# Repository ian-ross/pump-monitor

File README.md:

# pump-monitor
IoT system for pump shaft monitoring

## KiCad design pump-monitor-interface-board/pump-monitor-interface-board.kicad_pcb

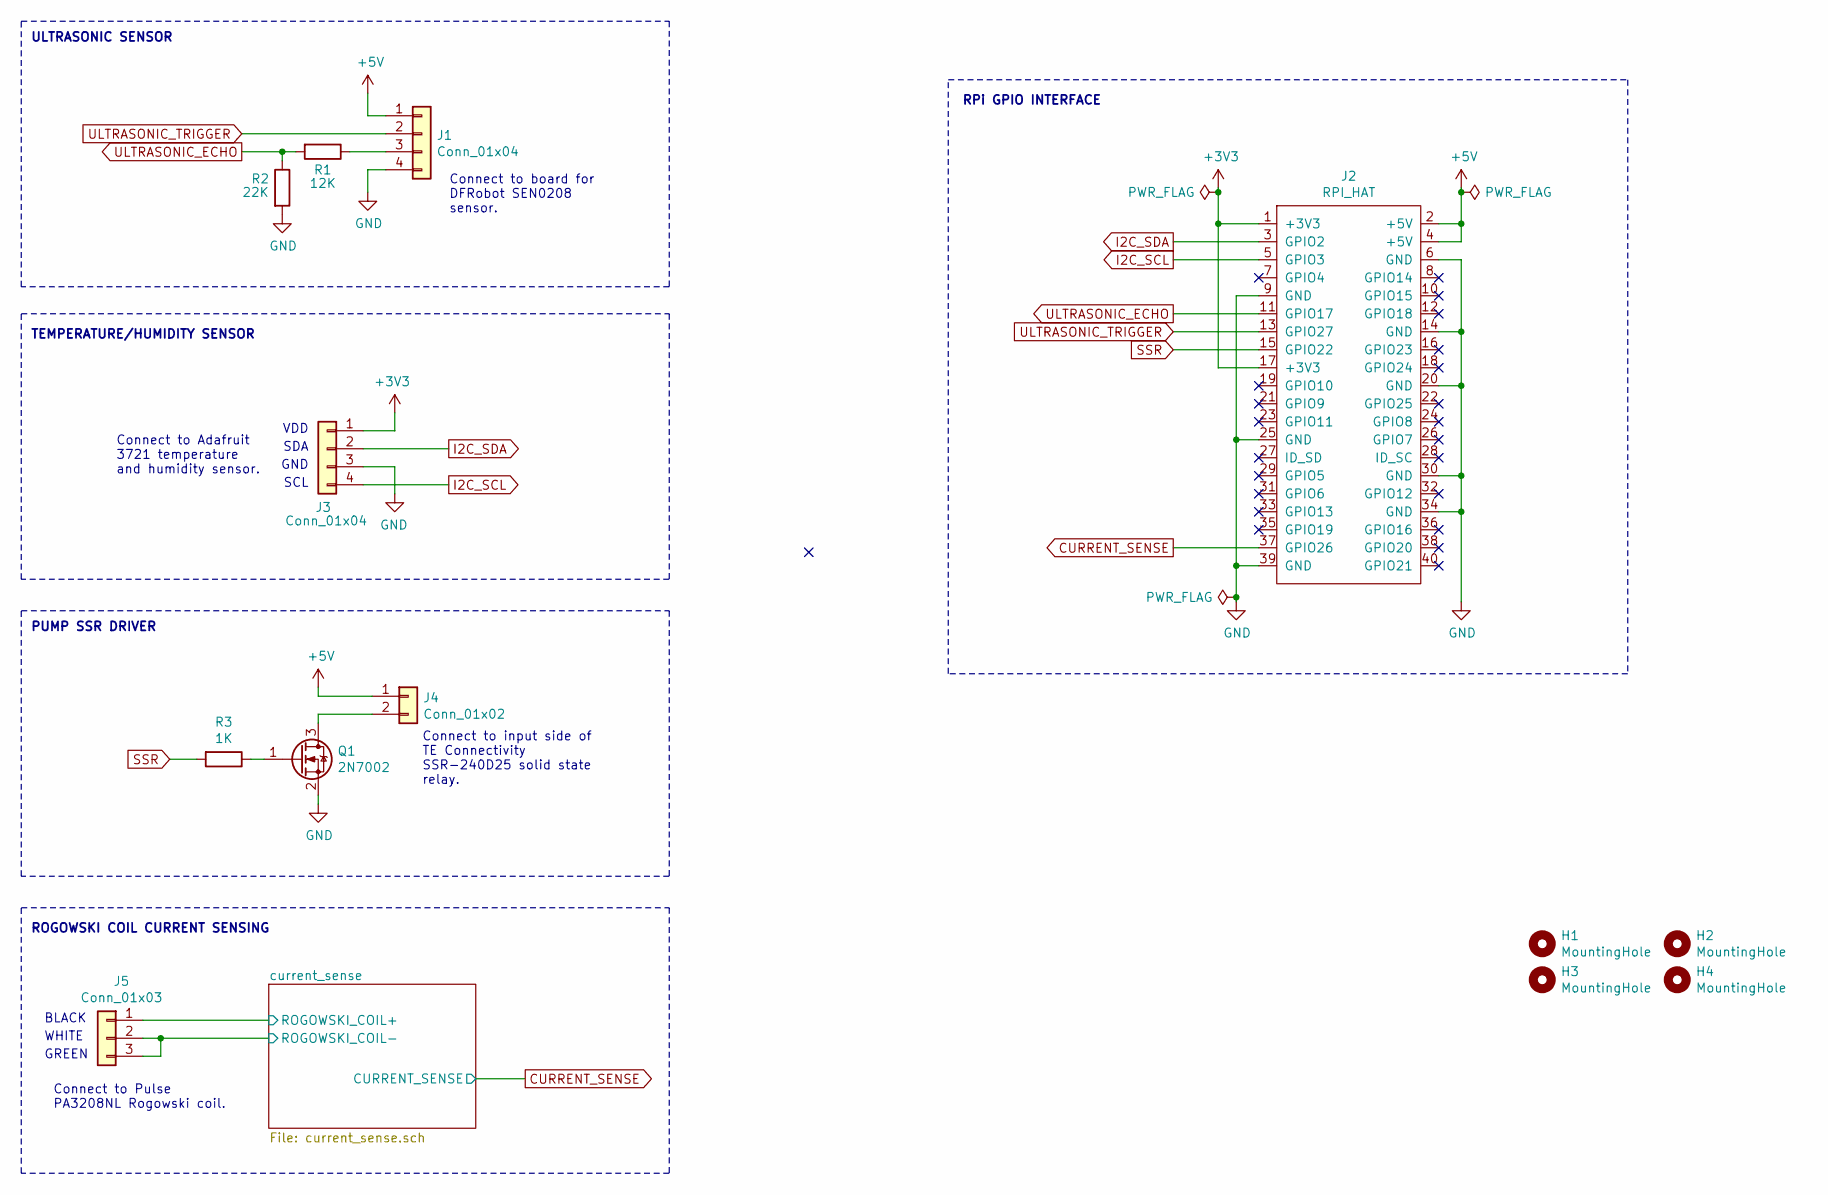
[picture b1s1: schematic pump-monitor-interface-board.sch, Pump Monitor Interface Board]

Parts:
H1, H2, H3, H4: MountingHole; MountingHole_2.7mm_M2.5; MPN n/a
J1, J3: Conn_01x04; PinHeader_1x04_P2.54mm_Horizontal; MPN TSW-104-25-T-S-RA
J2: RPI_HAT; PinSocket_2x20_P2.54mm_Vertical; MPN SSQ-120-01-L-D
J4: Conn_01x02; PinHeader_1x02_P2.54mm_Horizontal; MPN TSW-102-25-T-S-RA
J5: Conn_01x03; PinHeader_1x03_P2.54mm_Horizontal; MPN TSW-103-25-F-S-RA
Q1: 2N7002; SOT-23; MPN 2N7002ET7G
R1: 12K; R_0805_2012Metric_Pad1.20x1.40mm_HandSolder; MPN CRCW080512K0FKEA
R2: 22K; R_0805_2012Metric_Pad1.20x1.40mm_HandSolder; MPN CRCW080522K0FKEAC
R3: 1K; R_0805_2012Metric_Pad1.20x1.40mm_HandSolder; MPN CRGP0805F1K0

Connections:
+2V5: J5.2, J5.3; also elsewhere on the board
+3V3: J2.1 (+3V3), J2.17 (+3V3), J3.1
+5V: J1.1, J2.2 (+5V), J2.4 (+5V), J4.1; also elsewhere on the board
/current_sense/ROGOWSKI_COIL+: J5.1; also elsewhere on the board
CURRENT_SENSE: J2.37 (GPIO26); also elsewhere on the board
GND: J1.4, J2.6 (GND), J2.9 (GND), J2.14 (GND), J2.20 (GND), J2.25 (GND), J2.30 (GND), J2.34 (GND), J2.39 (GND), J3.3, Q1.2 (S), R2.2; also elsewhere on the board
I2C_SCL: J2.5 (GPIO3), J3.4
I2C_SDA: J2.3 (GPIO2), J3.2
unnamed: J1.3, R1.1
unnamed: J4.2, Q1.3 (D)
unnamed: Q1.1 (G), R3.1
SSR: J2.15 (GPIO22), R3.2
ULTRASONIC_ECHO: J2.11 (GPIO17), R1.2, R2.1
ULTRASONIC_TRIGGER: J1.2, J2.13 (GPIO27)

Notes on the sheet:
Connect to Pulse PA3208NL Rogowski coil.
RPi GPIO INTERFACE
BLACK
WHITE
GREEN
ROGOWSKI COIL CURRENT SENSING
PUMP SSR DRIVER
TEMPERATURE/HUMIDITY SENSOR
ULTRASONIC SENSOR
VDD
SDA
GND
SCL
Connect to Adafruit 3721 temperature and humidity sensor.
Connect to input side of TE Connectivity SSR-240D25 solid state relay.
Connect to board for DFRobot SEN0208 sensor.

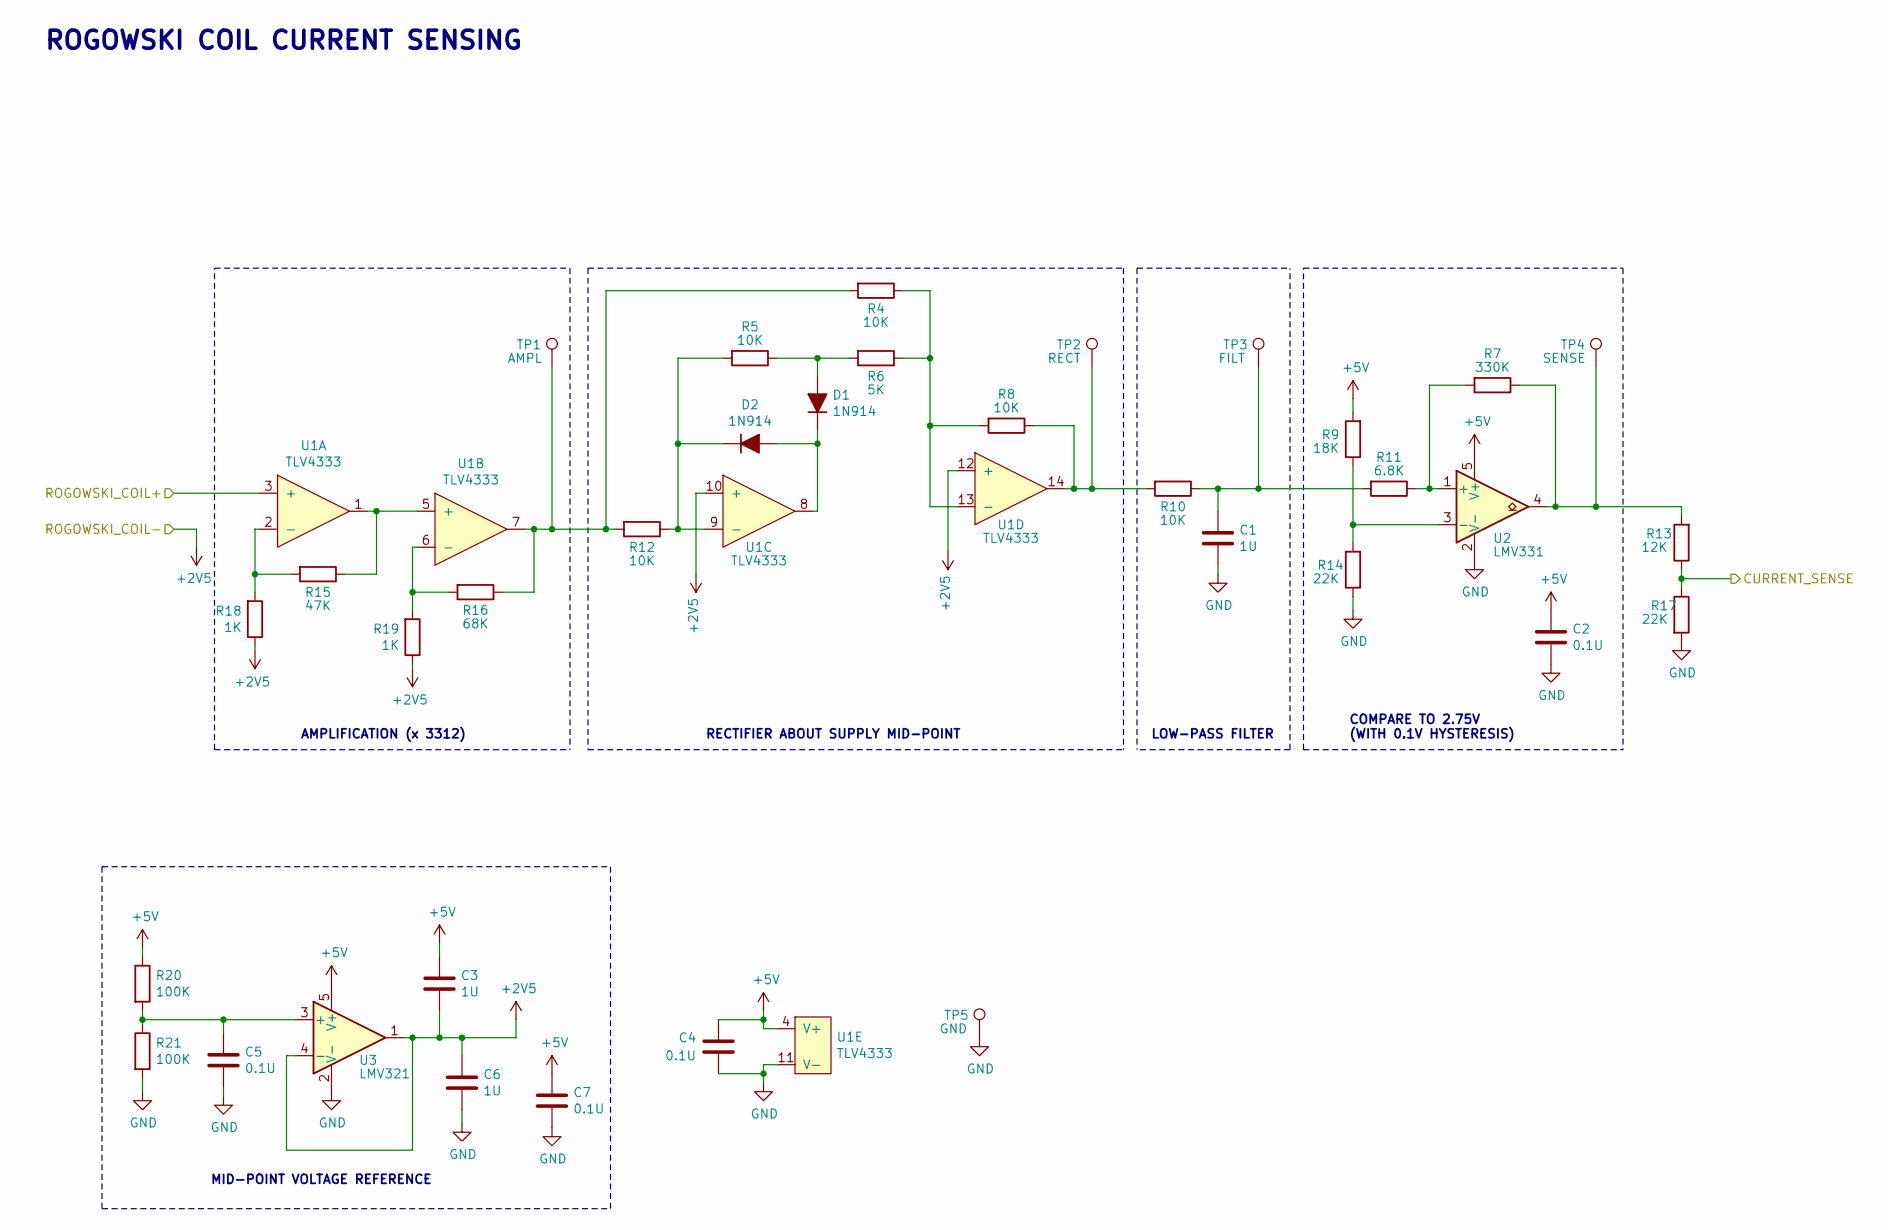
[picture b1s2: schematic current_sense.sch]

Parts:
C1, C3, C6: 1U; C_0805_2012Metric_Pad1.18x1.45mm_HandSolder; MPN 885012107015
C2, C4, C5, C7: 0.1U; C_0805_2012Metric_Pad1.18x1.45mm_HandSolder; MPN 885012207098
D1, D2: 1N914; D_SOD-123F; MPN 1N914BW RH
R4, R5, R8, R10, R12: 10K; R_0805_2012Metric_Pad1.20x1.40mm_HandSolder; MPN CRGP0805F10K
R6: 5K; R_0805_2012Metric_Pad1.20x1.40mm_HandSolder; MPN CRCW08055K00FKTA
R7: 330K; R_0805_2012Metric_Pad1.20x1.40mm_HandSolder; MPN CRCW0805330KFKEA
R9: 18K; R_0805_2012Metric_Pad1.20x1.40mm_HandSolder; MPN CRGP0805F18K
R11: 6.8K; R_0805_2012Metric_Pad1.20x1.40mm_HandSolder; MPN CRCW08056K80FKEA
R13: 12K; R_0805_2012Metric_Pad1.20x1.40mm_HandSolder; MPN CRCW080512K0FKEA
R14, R17: 22K; R_0805_2012Metric_Pad1.20x1.40mm_HandSolder; MPN CRCW080522K0FKEAC
R15: 47K; R_0805_2012Metric_Pad1.20x1.40mm_HandSolder; MPN CRCW080547K0FKEAC
R16: 68K; R_0805_2012Metric_Pad1.20x1.40mm_HandSolder; MPN CRCW080568K0FKEA
R18, R19: 1K; R_0805_2012Metric_Pad1.20x1.40mm_HandSolder; MPN CRGP0805F1K0
R20, R21: 100K; R_0805_2012Metric_Pad1.20x1.40mm_HandSolder; MPN CRCW0805100KFKEAC
TP1: AMPL; TestPoint_Keystone_5000-5004_Miniature; MPN n/a
TP2: RECT; TestPoint_Keystone_5000-5004_Miniature; MPN n/a
TP3: FILT; TestPoint_Keystone_5000-5004_Miniature; MPN n/a
TP4: SENSE; TestPoint_Keystone_5000-5004_Miniature; MPN n/a
TP5: GND; TestPoint_Keystone_5000-5004_Miniature; MPN n/a
U1: TLV4333; SO-14_3.9x8.65mm_P1.27mm; MPN TLV4333IDR
U2: LMV331; SOT-23-5_HandSoldering; MPN LMV331IDBVR
U3: LMV321; SOT-23-5_HandSoldering; MPN LMV321AIDBVR

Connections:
+2V5: C3.2, C6.1, R18.1, R19.1, U1.10 (+), U1.12 (+), U3.1, U3.4 (-); also elsewhere on the board
+5V: C2.1, C3.1, C4.1, C7.1, R9.2, R20.1, U1.4 (V+), U2.5 (V+), U3.5 (V+); also elsewhere on the board
/current_sense/ROGOWSKI_COIL+: U1.3 (+); also elsewhere on the board
CURRENT_SENSE: R13.1, R17.1; also elsewhere on the board
GND: C1.2, C2.2, C4.2, C5.2, C6.2, C7.2, R14.1, R17.2, R21.2, TP5.1, U1.11 (V-), U2.2 (V-), U3.2 (V-); also elsewhere on the board
unnamed: C1.1, R10.1, R11.2, TP3.1
unnamed: C5.1, R20.2, R21.1, U3.3 (+)
unnamed: D1.1 (K), D2.2 (A), U1.8
unnamed: D1.2 (A), R5.1, R6.2
unnamed: D2.1 (K), R5.2, R12.1, U1.9 (-)
unnamed: R4.1, R6.1, R8.2, U1.13 (-)
unnamed: R8.1, R10.2, TP2.1, U1.14
unnamed: R7.2, R11.1, U2.1 (+)
unnamed: R4.2, R12.2, R16.1, TP1.1, U1.7
unnamed: R7.1, R13.2, TP4.1, U2.4
unnamed: R9.1, R14.2, U2.3 (-)
unnamed: R15.1, U1.1, U1.5 (+)
unnamed: R15.2, R18.2, U1.2 (-)
unnamed: R16.2, R19.2, U1.6 (-)

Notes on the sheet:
AMPLIFICATION (x 3312)
RECTIFIER ABOUT SUPPLY MID-POINT
LOW-PASS FILTER
COMPARE TO 2.75V (WITH 0.1V HYSTERESIS)
ROGOWSKI COIL CURRENT SENSING
MID-POINT VOLTAGE REFERENCE

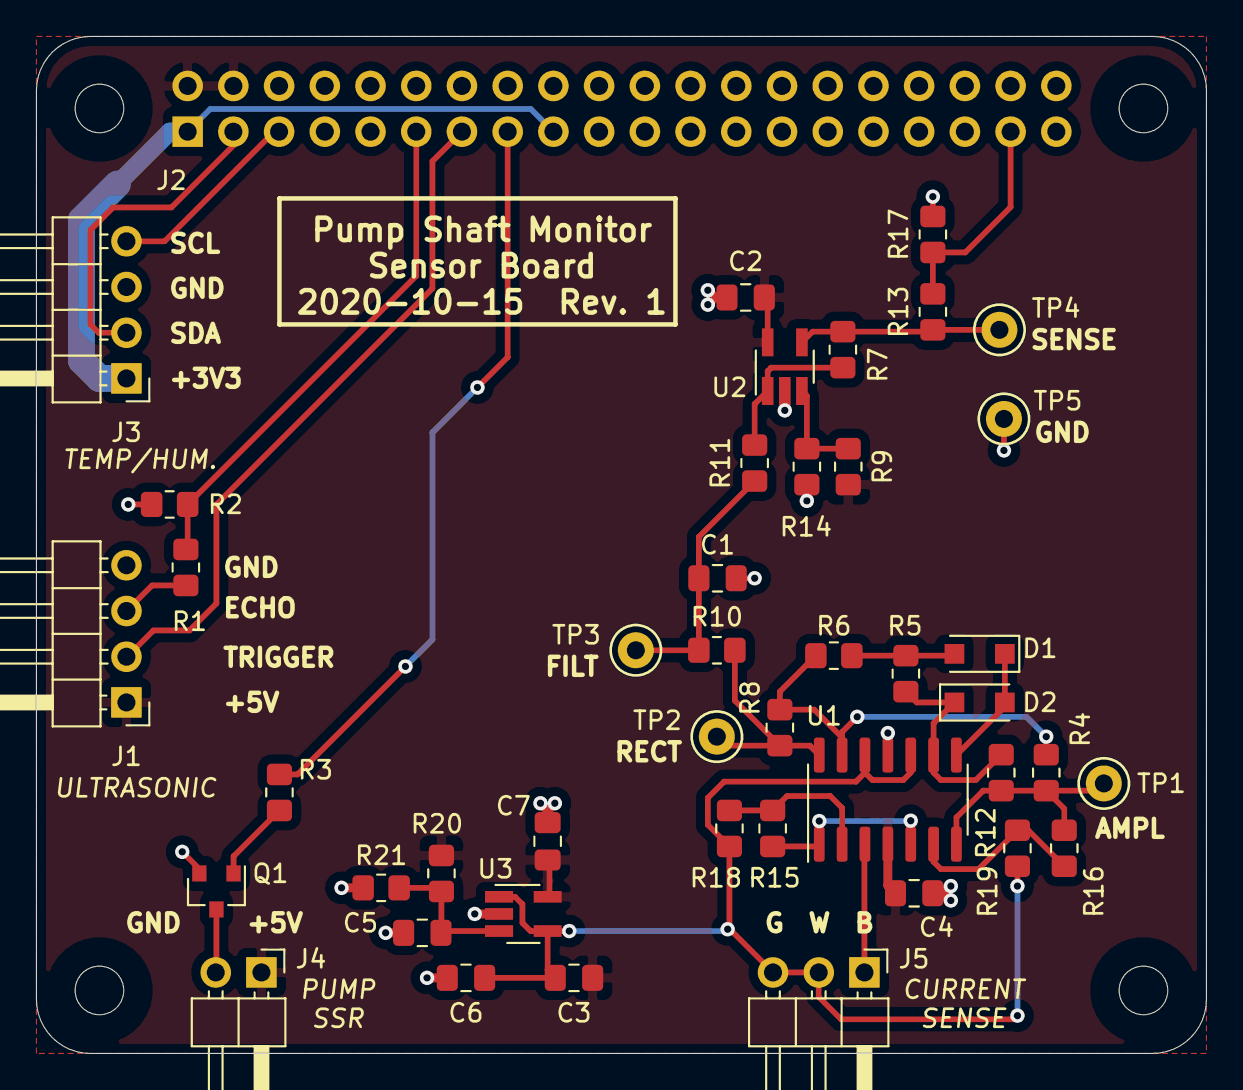
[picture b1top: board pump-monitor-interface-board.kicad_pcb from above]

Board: 2 copper layers, 65.0 x 56.5 mm, 48 parts (1 on the bottom side), 28 nets.

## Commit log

2020-10-15 Interface board layout done
2020-10-22 Design checklists
2020-12-14 Add ultrasonic sensor driver as submodule
2020-12-14 Tidying
2020-12-14 PDF schematic of interface board
